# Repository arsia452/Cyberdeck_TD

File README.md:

# Cyberdeck TD Project

## Overview + goal of project
Cyberdeck Project: The main goal is to create a "cyberdeck"; essentially a laptop with personalized functionality, based around the LattePanda Mu compute module.

---

## Main Systems:

### LattePanda Mu Custom Carrier Board:
The cyberdeck is to include a custom carrier PCB to fit the size, needs, and power constraints of the user
- HDMI output
- PCIe M-key for M.2-2230 PCIe 3.0x1 NVMe SSD
- PCIe E-key for Wi-Fi capabilities
- 2x USB-A 2.0 ports
- 2x USB-A 3.2 ports
- GbE (1000Mbps) RJ45 port 
- RTC using CR2032 as CMOS battery

### Custom Keyboard:
The cyberdeck is to include a custom keyboard which can connect over both Bluetooth and an internal 4pin to USB cable.
- Connect over both Bluetooth and USB | Will be achieved using an nRF52840 SoC (henceforth "MCU")
- Built in 1100mAh battery | Will be achieved by using a 2-pin JST connector on the keyboard PCB which powers the MCU and supports USB-C charging
- USB-C connection for both data and charging | Will be achieved by a USB-C port mounted to the keyboard PCB which will allow for both data transmission and charging
- Run ZMK to handle logic and keyboard matrix | Will be achieved by programming the aforementioned MCU and flashing the open-source software to the onboard flash memory

### Battery:
The cyberdeck is to include a built in (~100Wh) battery with safe (but fast) power path charging (can be both on and charging at the same time) and USB-C hot-plug support.
- 100Wh battery | Will be achieved with a Tenergy 14.4V 7000mAh battery pack consisting of 18650 cells in a 4S2P architecture
- Integrated power path charger | Will be achieved with an LTC4612-L42 IC on the main carrier PCB, allowing for smart switching between USB-C system power + charging and exclusive battery power upon plugging in/unplugging the charging cable

### 11.6" Touchscreen:
The cyberdeck is to integrate a 11.6" touchscreen in the housing as well as optional external display.
- Built-in screen | Will be achieved with a DFRobot eDP 11.6" touchscreen to allow for "Microsoft Surface/iPad"-esque capabilities
- External optional display | Will be achieved through HDMI port and software options to allow for mirroring or second monitor extension (1)

### Enclosure:
The cyberdeck is to be enclosed in an enclosure no larger in footprint than a standard laptop (2)
- Custom main enclosure made of machined aluminum and FDM-based 3D printed PLA (3) | Will be achieved with a mixture of outsourced machining capabilities (PCBWay, JLCPCB, etc.) for the aluminum and home 3D printing
- Custom keyboard enclosure made of 3D printed PLA | Will be achieved using home 3D printing capabilities and heat-set inserts to provide increased rigidity.

### Footnotes:

(1) Though, that is pushing the capabilities of the compute module itself

(2) Excluding thickness; that is for a later revision and would require a custom cooling solution, new battery design, and various other technical capabilities that are presently out of reach.

(3) The use of PLA may shift to ABS down the line if the capabilities introduce themselves, but the Bambu Labs A1 I have will not reliably print ABS in open-air environments as ABS is very prone to stringing and deformation in atmospheric conditions. This applies to all mentions of PLA in this project.

---

## Main Components
Excludes passives (Capacitors, diodes, etc.) and materials (PLA, aluminum, solder etc.)
- Main Compute Module | LattePanda Mu
- Development Carrier Board | DFRobot LattePanda Mu Carrier Board Lite (for development and testing purposes)
- Screen | DFRobot 11.6" eDP Touchscreen
- Keyboard PCB | Custom PCB
- Carrier Board PCB | Custom PCB
- Trackpad Module | Azoteq TPS43 
- Keyboard MCU | MDBT50Q-1MV2 (Nordic nRF52840 based SoC)
- Key Switches | Kailh Choc Blue V2
- Keycaps | Undetermined
- Enclosures | Custom designed multi-piece aluminum and PLA construction
- Wi-Fi card | Intel BE200 Wi-Fi 7 and Bluetooth 5.4
- Powerpath Charging | Analog Devices LTC4162-L42 IC
- USB-C Power Delivery | WCH CH224K IC for 20V input
- 3.3V and 5V regulation | Silergy SY8253ADC IC
- Gigabit Ethernet | Realtek RTL8111H-CG
- Sound | Analog Devices MAX98365

---

## Currently Developed:

### Custom Carrier Board:
The carrier board is currently in development. It is now in the final main step; peer review. The ports, SODIMM slot, RTC battery, and battery screw terminal placements are more or less finalized. There may be slight shifts as the development of the enclosure progresses in order to accommodate the screen, keyboard, and battery. The carrier PCB may or may not end up including audio, as I am unsure if the I2S built into the module actually works. Last I heard, it was still in development by DFRobot, so I may need to use USB audio or simply forego internal audio altogether, though that is not ideal.

#### Carrier Board Length Matching:
=-=-=-=-=-=-=- Length Matching -=-=-=-=-=-=-=
Order of precedence:

=-=-=-=-=-=-=- E-key  -=-=-=-=-=-=-=
All in one area  (<0.127mm skew) (0.1704mm trace width):
- CON_PCIE_TX_0 
[0.0000mm] + [0.0000mm] = [0.0000mm] total skew
[2.5690mm] + [104.0946mm] = [106.6636mm] total length

- HSIO_3_RX
[0.0000mm] total skew
[82.0600mm] total length

- REFCLK3
[0.0000mm] total skew
[66.8870mm] total length

=-=-=-=-=-=-=- M-key  -=-=-=-=-=-=-=
All in one area  (<0.127mm skew) (0.1704mm trace width):
- CON_PCIE_TX_1
[0.0000mm] + [0.0000mm] = [0.0000mm] total skew
[2.7606mm] + [109.3664mm] = [112.1270mm] total length

- HSIO_2_RX
[0.0000mm] total skew
[88.0080mm] total length

- REFCLK0
[0.0000mm] total skew
[149.2008mm] total length

=-=-=-=-=-=-=- GbE  -=-=-=-=-=-=-=
All in one area  (<0.127mm skew) (0.1704mm trace width):
- GbE_PCIe_TX 
[0.0055mm] + [0.0000mm] = [0.0055mm] total skew
[1.8168mm] +  [55.2107mm] = [57.0275mm] total length

- GbE_PCIe_RX
[0.0001mm] +  [0.0000mm] = [0.0001mm] total skew
[3.9770mm] +  [49.1530mm] = [53.1300.mm] total length

- GbE_PCIe_CLK
[0.0005mm] total skew
[52.5019mm] total length

 =-=-=-=-=-=-=- HDMI  -=-=-=-=-=-=-=
All in one area (0.10 - 0.15mm skew with pairs also roughly all the same length) (0.1704mm trace width):

The brackets below are in order from HDMI connector to Mu and all of the sub-traces in between the passives.

- DDI_B_TX0 
[0.0001mm] + [0.0000mm] + [0.0001mm] + [0.0000mm] = [0.0002mm] total skew
[3.5389mm] + [4.1628mm] + [4.4761mm] + [94.2515mm] = [106.4293mm] total length

- DDI_B_TX1
[0.0001mm] + [0.0001mm] + [0.0001mm] + [0.0000mm] = [0.0003mm] total skew
[3.5409mm] + [3.7013mm] + [3.9786mm] + [94.2766mm] = [105.4974mm] total length

- DDI_B_TX2
[0.0001mm] + [0.0001mm] + [0.0000mm] + [0.0000mm] = [0.0002mm] total skew
[3.5182mm] + [3.5178mm] + [4.0990mm] + [94.2152mm] = [105.3502mm] total length

- DDI_B_TX3
[0.0001mm] + [0.0000mm] + [0.0001mm] + [0.0000mm] = [0.0002mm] total skew
[3.5170mm] + [4.1919mm] + [4.1763mm] + [94.2153mm] = [106.1005] total length

=-=-=-=-=-=-=- USB3.2  -=-=-=-=-=-=-=
All in one area  (<0.10mm skew) (0.1704mm trace width):
- HSIO_0_TX
[0.0100mm] + [0.0000mm] + [0.0000mm] = [0.0100mm] total skew
[8.8612mm] + [5.3635mm] + [54.0231mm] = [68.2478mm] total length

- HSIO_1_TX
[0.0027mm] + [0.0000mm] + [0.0000mm] = [0.0027mm] total skew
[3.9047mm] + [5.4568mm] + [54.7050mm] = [64.0665mm] total length

- CON_USB3_D 
[0.0000mm] + [0.0000mm] = [0.0000mm] total skew
[29.9915mm] + [84.4885mm] = [114.48mm] total length

- CON_USB4_D
[0.0001mm] + [0.0000mm] = [0.0000mm] total skew
[7.2915mm] + [73.4302mm] = [80.7217mm] total length

- CON_USB3_SSRX
[0.0000mm] + [0.0000mm] = [0.0000mm] total skew
[9.2867mm] + [51.9657mm] = [61.2524mm] total length

- CON_USB4_SSRX
[0.0000mm] + [0.0000mm] = [0.0000mm] total skew
[3.4665mm] + [52.8293mm] = [56.2958mm] total length

=-=-=-=-=-=-=- E-key USB  -=-=-=-=-=-=-=
(<0.10mm skew) (0.1704mm trace width):
- USB_2_P7
[0.0000mm] total skew
[79.0188mm] total length

=-=-=-=-=-=-=- USB2.0  -=-=-=-=-=-=-=
All in one area  (<0.10mm skew (0.1704mm trace width)):
- CON_USB2_D
[0.0000mm] total skew
[59.4753mm] total length

- CON_USB1_D
[0.0000mm] total skew
[66.1903] total length

### Custom Keyboard:
The keyboard PCB is ready for fabrication as soon as the financials make sense. Some other minor modifications may be made based on any lessons learned from the carrier board as development of the two is parallel, but the design is essentially finalized.

### Enclosure
The enclosure itself is the least developed portion of the project thus far. The only thing that it is right now is a couple of STEP models in Fusion360 haphazardly slapped into a shape. 

The keyboard enclosure has been mocked up, but fastening the keyboard enclosure parts together and mounting the keyboard to the main enclosure are still unsolved challenges at this time. Potential approaches for the fastening problem include screws with heat-set inserts, flexible plastic clips, panel clips, snap together clips, or others. The keyboard is currently one massive assembly, but this is infeasible for the 3D printer that I own, and thus must be redesigned from the ground up. A 2-piece assembly is ideal, but a 3-piece assembly will offer more mechanisms to fasten the components together.

### Footnotes: 

(1) Ideally, one chassis part is preferable, but this is likely unfeasible due to home 3D printing size constraints. I will see what I can make happen. Same note as before about PLA/ABS.

---

## Currently in Development:

### Custom Carrier Board:
The battery charging circuitry is yet to be tested, but this will be tested on a standalone PCB with the battery pack I intend to use well before the custom carrier board is finalized for production to ensure that there is no... expedited expulsion of excited electrons and/or lithium due to an incorrect understanding of power-path battery charging and high-side load switching.

### Custom Keyboard:
The MCU, trackpad module, and key switches are currently in the mail (as of 10/16/2026) for further hands-on testing before finalizing the PCB order to ensure proper fit, function, and pinouts as it relates to the MCU _before_ it is set in stone (or fiberglass and copper, I suppose).

### Enclosure
Cooling will be essential, as the battery, compute module and screen will be in the same enclosure in very close proximity to each other. Using an aluminum subframe to diffuse the heat is a possibility, but will require further investigation and development time. The main idea is a five piece enclosure consisting of: faceplate (black anodized aluminum), left side bracket (orange anodized aluminum), right side bracket (orange anodized aluminum), rear main chassis (black 3D printed PLA), front main chassis (black 3D printed PLA) (1)

The keyboard is currently one massive assembly, but this is infeasible for the 3D printer that I own, and thus must be redesigned from the ground up. A 2-piece assembly is ideal for rigidity and simplicity, but a 3-piece assembly will offer more mechanisms to fasten the components together, smaller prints for faster iterative design efforts, and overall more options for design. The 3-piece design is more likely. Fastening the keyboard enclosure parts together and mounting the keyboard to the main enclosure are still unsolved challenges at this time. Potential approaches for the fastening problem include screws with heat-set inserts, flexible plastic clips, panel clips, snap together clips, or others. 3D modeling is not yet something I am very good at, so this will be a good chance to improve my skills in a useful and fun way. Potential approaches to the mounting issue are rails, slots, or grooves on the main enclosure that the keyboard slides into, magnets, or others.

### Footnotes: 

(1) Ideally, one main chassis is preferable for the sake of rigidity and solid construction feel, but this is likely unfeasible due to home 3D printing size constraints. I will see what I can make happen. Same note as before about PLA/ABS.

---

## Future of Development/Improvements for Next Iteration:

---

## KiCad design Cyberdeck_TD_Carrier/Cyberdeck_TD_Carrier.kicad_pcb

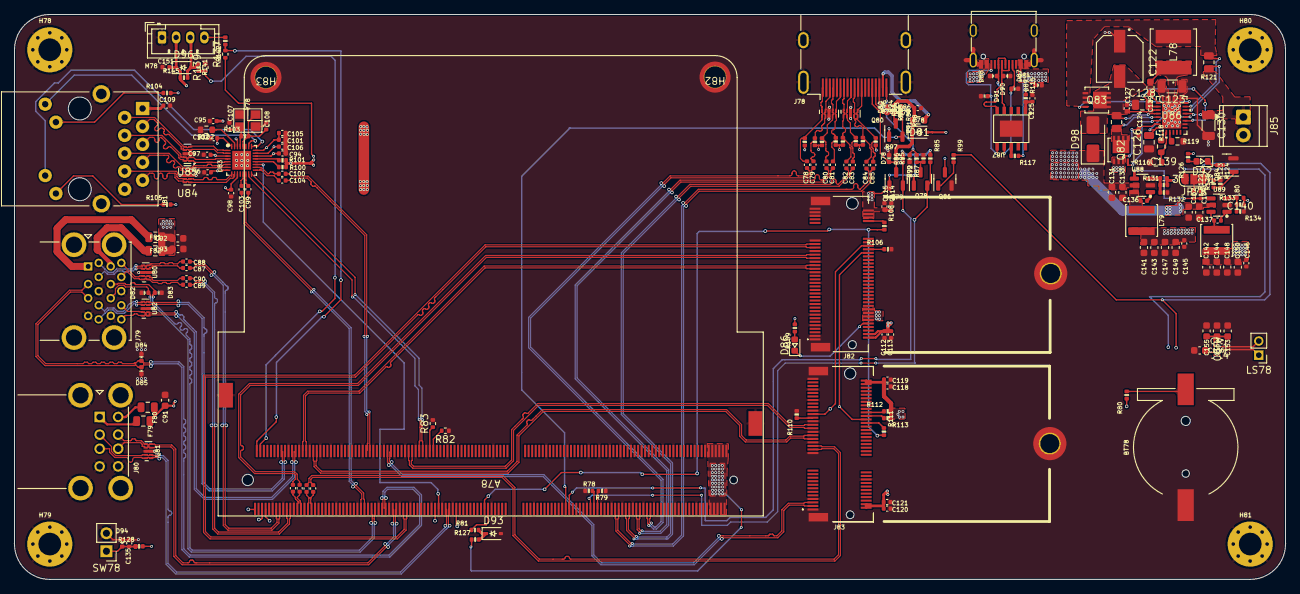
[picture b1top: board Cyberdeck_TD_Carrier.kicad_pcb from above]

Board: 4 copper layers, 180.0 x 80.0 mm, 205 parts (0 on the bottom side), 166 nets.

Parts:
A78: LattePanda_Mu; LattePanda_Module_H8.0mm_Horizontal
BT78: Battery_Cell; Battery_Holder_CR1220_S8411-45R
C78, C79, C80, C81, C82, C83, C84, C85, C86, C87, C88, C89, C90, C94, C95, C96, C97, C98, C99, C100, C101, C102, C103, C104, C106, C109, C113, C115, C119, C121, C136, C137, C145, C146, C151: 100nF/50V; C_0402_1005Metric
C91, C92, C93, C131, C132, C133, C134, C141, C142, C143, C144, C147, C148, C149, C150: 22uF/10V; C_0603_1608Metric
C105, C112, C114, C118, C120: 10uF/10V; C_0402_1005Metric
C107, C108, C139, C140: 12pF/50V; C_0402_1005Metric
C110, C111, C116, C117: 220nF/50V; C_0402_1005Metric
C122: 47uF; CAP_EEEFH1E470XL
C123, C130: 10uF; C_1206_3216Metric
C124, C127: 0.1uF; C_0402_1005Metric
C125, C135: 1uF/16V; C_0402_1005Metric
C126: 1uF; C_0805_2012Metric
C128: 10uF; C_0805_2012Metric
C129: 22nF; C_0603_1608Metric
C153: 100uF; C_0603_1608Metric
C154: 10uF; C_0603_1608Metric
C155, C156: 1uF; C_0603_1608Metric
D78, D79, D80, D82, D83, D84, D85, D87, D88, D94: ESD5V0B03; D_0402_1005Metric
D81, D96: 1N5819WS; D_SOD-323
D86, D92: LED_G; LED_0603_1608Metric
D89, D90, D91: PESD24VS1UL-N; D_0402_1005Metric
D93: 3V3 Izt=5mA; D_SOD-323
D98: D_TVS; D_SMA
F78: 6V/50mA; R_0603_1608Metric
F79, F80: 6V/1A; Fuse_0805_2012Metric
F81: 6V/2A; R_0805_2012Metric
F82: 6V/2A; Fuse_0805_2012Metric
H78, H79, H80, H81: MountingHole_Pad; MountingHole_3.2mm_M3_Pad_Via
H82, H83: MountingHole_Pad; MountingHole_3mm_M2_Pad_TopOnly
H84, H85: MountingHole_M2.0; MountingHole_2.7mm_M2.5_DIN965_Pad_TopOnly
J78: HDMI_A; HDMI_A_Molex_208658-1001_Horizontal
J79: USB3_A_Stacked; USB3_A_Molex_48406-0001_Horizontal_Stacked
J80: USB_A_Stacked; USB_A_CUI_UJ2-ADH-TH_Horizontal_Stacked
J81: RJ45_RB1-125B8G1A; RJ45_UDE_RB1-125B8G1A
J82: Bus_M.2_Socket_M; PCIe_M.2_Connectors_P=0.5mm_H=4.2mm_KeyM
J83: Bus_M.2_Socket_E; PCIe_M.2_Connectors_P=0.5mm_H=4.2mm_KeyE
J84: USB_C_Receptacle_USB2.0; USB_C_Receptacle_G-Switch_GT-USB-7010ASV
J85: BAT_TERM; TerminalBlock_TE_282834-2_1x02_P2.54mm_Horizontal
JP78: SolderJumper_3_Open; SolderJumper-3_P1.3mm_Bridged2Bar12_RoundedPad1.0x1.5mm_Num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
L78: 4.7uH; IND_VLS6045EX-4R7M_TDK
L79, L80: 2.2uH/4.3A; L_Sunlord_SWPA4020S
LS78: Speaker; PinHeader_1x02_P2.00mm_Vertical
M78: Fan_4pin; JST_PH_B4B-PH-K_1x04_P2.00mm_Vertical
Q78, Q84: 2N7002; SOT-23
Q79, Q80, Q81: 2SK3018; SOT-23
Q82, Q83: FDMC8327L; WDFN8_511DR_OSI
R78, R79, R125: 100K/1%; R_0402_1005Metric
R80, R92, R115, R123: 1K/1%; R_0402_1005Metric
R81, R82, R83, R100, R101, R112, R113, R117, R124, R132: 10K/1%; R_0402_1005Metric
R84, R86, R95, R98, R99, R109, R126, R127: 2.2K/1%; R_0402_1005Metric
R85, R103: 1M/1%; R_0402_1005Metric
R87, R133, R139, R141: 21.5K/1%; R_0402_1005Metric
R88, R89, R90, R91, R93, R94, R96, R97, R104, R105: 470R/1%; R_0402_1005Metric
R102: 2.49K/1%; R_0603_1608Metric
R106, R108, R110, R111: 0R/1%; R_0402_1005Metric
R114: 6.8mΩ; R_0805_2012Metric
R116, R118: 10kΩ; R_0603_1608Metric
R119: 63.4kΩ; R_0603_1608Metric
R121: 10mΩ; R_0805_2012Metric
R122, R128, R142: 100R/1%; R_0402_1005Metric
R131: 75K/1%; R_0402_1005Metric
R134, R137, R145: 4.7K/1%; R_0402_1005Metric
SW78: PWR_BTN; PinHeader_1x02_P2.54mm_Vertical
U78, U79: TPAZ1023-04F; Diodes_UDFN-10_1.0x2.5mm_P0.5mm
U80, U81, U82, U84, U85: ULC0524P; Diodes_UDFN-10_1.0x2.5mm_P0.5mm
U83: RTL8111H-CG-RH; QFN-32-1EP_4x4mm_P0.4mm_EP2.65x2.65mm
U86: LTC4162-L42; 05-08-1712_ADI-L
U87: CH224K; ESSOP-10-1EP_3.9x5mm_P1.0mm_EP3.2x2.3
U88, U89: SY8253ADC; TSOT-23-6
U90: MAX98365AEWC+; 21-100536_W121D1&plus_1_MXM
Y78: 25MHz; Crystal_SMD_3225-4Pin_3.2x2.5mm

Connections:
5V_HDMI_VCC: C86.1, D81.1 (K), F78.1, R95.1, R98.1
+1V0: C94.2, C95.2, C96.2, C97.2, C101.2, C105.2, U83.3 (AVDD10), U83.8 (AVDD10), U83.22 (DVDD10), U83.24 (REGOUT), U83.30 (AVDD10)
+3V3: C98.2, C102.2, C106.2, C112.2, C113.2, C114.2, C115.2, C118.2, C119.2, C120.2, C121.2, C140.1, C142.2, C144.2, C146.1, C148.2, C150.2, J82.2 (3.3V), J82.4 (3.3V), J82.12 (3.3V), J82.14 (3.3V), J82.16 (3.3V), J82.18 (3.3V), J82.70 (3.3V), J82.72 (3.3V), J82.74 (3.3V), J83.2 (3.3V), J83.4 (3.3V), J83.72 (3.3V), J83.74 (3.3V), L80.2, Q78.1 (G), Q79.1 (G), Q80.1 (G), R84.1, R85.1, R86.1, R100.1, R101.1, R104.2, R105.2, R109.2, R112.2, R113.1, R126.2, R133.2, R137.1, U83.11 (AVDD33), U83.23 (VDDREG), U83.32 (AVDD33)
+5V: C91.2, C92.2, C93.2, C139.1, C141.2, C143.2, C145.1, C147.2, C149.2, C151.1, D81.2 (A), D96.1 (K), F79.1, F80.1, F81.1, F82.1, L79.2, M78.2 (+), R131.2, R145.1
+BATT: A78.115 (VBAT), R80.1
/Fan_Temp/FAN_1_PWM: A78.2 (FAN1_PWM), R137.2, R142.1
/Fan_Temp/FAN_1_TAC: A78.4 (FAN1_TAC), R139.1, R141.2
/Gigabit Ethernet/GbE_PCIe_CLK+: A78.94 (REFCLK4+), U83.15 (REFCLK_P)
/Gigabit Ethernet/GbE_PCIe_CLK-: A78.96 (REFCLK4-), U83.16 (REFCLK_N)
/Gigabit Ethernet/GbE_PCIe_RX+: A78.64 (HSIO6_RX+), C104.2
/Gigabit Ethernet/GbE_PCIe_RX-: A78.66 (HSIO6_RX-), C100.2
/Gigabit Ethernet/GbE_PCIe_TX+: A78.61 (HSIO6_TX+), C103.2
/Gigabit Ethernet/GbE_PCIe_TX-: A78.63 (HSIO6_TX-), C99.2
/Gigabit Ethernet/HSI+: C103.1, U83.13 (HSIP)
/Gigabit Ethernet/HSI-: C99.1, U83.14 (HSIN)
/Gigabit Ethernet/HSO+: C104.1, U83.17 (HSOP)
/Gigabit Ethernet/HSO-: C100.1, U83.18 (HSON)
/Gigabit Ethernet/LED1_1000: J81.L4, U83.26 (LED1)
/Gigabit Ethernet/LED2_ACT: J81.L2, U83.25 (LED2)
/Gigabit Ethernet/MDI0+: J81.R2 (TD1+), U83.1 (MDIP0), U85.5, U85.6 (NC)
/Gigabit Ethernet/MDI0-: J81.R3 (TD1-), U83.2 (MDIN0), U85.4, U85.7 (NC)
/Gigabit Ethernet/MDI1+: J81.R4 (TD2+), U83.4 (MDIP1), U85.2, U85.9 (NC)
/Gigabit Ethernet/MDI1-: J81.R5 (TD2-), U83.5 (MDIN1), U85.1, U85.10 (NC)
/Gigabit Ethernet/MDI2+: J81.R6 (TD3+), U83.6 (MDIP2), U84.5, U84.6 (NC)
/Gigabit Ethernet/MDI2-: J81.R7 (TD3-), U83.7 (MDIN2), U84.4, U84.7 (NC)
/Gigabit Ethernet/MDI3+: J81.R8 (TD4+), U83.9 (MDIP3), U84.2, U84.9 (NC)
/Gigabit Ethernet/MDI3-: J81.R9 (TD4-), U83.10 (MDIN3), U84.1, U84.10 (NC)
/HDMI/DDC_SCL: D78.2 (A2), J78.15 (SCL), Q79.3 (D), R95.2
/HDMI/DDC_SDA: D80.2 (A2), J78.16 (SDA), Q80.3 (D), R98.2
/HDMI/DDI_B_DDC_SCL: A78.171 (DDIB_DDC_SCL), Q79.2 (S), R86.2
/HDMI/DDI_B_DDC_SDA: A78.169 (DDIB_DDC_SDA), Q80.2 (S), R84.2
/HDMI/DDI_B_HPD: A78.183 (DDIB_HPD), Q78.2 (S), R85.2
/HDMI/DDI_B_TX0+: A78.217 (DDIB_TX0+), C78.1
/HDMI/DDI_B_TX0-: A78.215 (DDIB_TX0-), C79.1
/HDMI/DDI_B_TX1+: A78.211 (DDIB_TX1+), C80.1
/HDMI/DDI_B_TX1-: A78.209 (DDIB_TX1-), C81.1
/HDMI/DDI_B_TX2+: A78.205 (DDIB_TX2+), C82.1
/HDMI/DDI_B_TX2-: A78.203 (DDIB_TX2-), C83.1
/HDMI/DDI_B_TX3+: A78.199 (DDIB_TX3+), C84.1
/HDMI/DDI_B_TX3-: A78.197 (DDIB_TX3-), C85.1
/HDMI/HPD: D79.2 (A2), J78.19 (HPD), R92.2
/HDMI/TMDS_CK+: C84.2, J78.10 (CK+), R89.1, U79.4, U79.7 (NC)
/HDMI/TMDS_CK-: C85.2, J78.12 (CK-), R88.1, U79.5, U79.6 (NC)
/HDMI/TMDS_D0+: C82.2, J78.7 (D0+), R91.1, U79.1, U79.10 (NC)
/HDMI/TMDS_D0-: C83.2, J78.9 (D0-), R90.1, U79.2, U79.9 (NC)
/HDMI/TMDS_D1+: C80.2, J78.4 (D1+), R94.1, U78.4, U78.7 (NC)
/HDMI/TMDS_D1-: C81.2, J78.6 (D1-), R93.1, U78.5, U78.6 (NC)
/HDMI/TMDS_D2+: C78.2, J78.1 (D2+), R97.1, U78.1, U78.10 (NC)
/HDMI/TMDS_D2-: C79.2, J78.3 (D2-), R96.1, U78.2, U78.9 (NC)
/LattePanda Module/HSIO_0_TX+: A78.13 (HSIO0_TX+), C88.1
/LattePanda Module/HSIO_0_TX-: A78.15 (HSIO0_TX-), C87.1
/LattePanda Module/HSIO_1_TX+: A78.19 (HSIO1_TX+), C90.1
/LattePanda Module/HSIO_1_TX-: A78.21 (HSIO1_TX-), C89.1
/LattePanda Module/HSIO_2_RX+: A78.28 (HSIO2_RX+), J82.43 (PERp0/SATA-B-)
/LattePanda Module/HSIO_2_RX-: A78.30 (HSIO2_RX-), J82.41 (PERn0/SATA-B+)
/LattePanda Module/HSIO_2_TX+: A78.25 (HSIO2_TX+), C110.1
/LattePanda Module/HSIO_2_TX-: A78.27 (HSIO2_TX-), C111.1
/LattePanda Module/HSIO_3_RX+: A78.34 (HSIO3_RX+), J83.41 (PERp0)
/LattePanda Module/HSIO_3_RX-: A78.36 (HSIO3_RX-), J83.43 (PERn0)
/LattePanda Module/HSIO_3_TX+: A78.31 (HSIO3_TX+), C116.1
/LattePanda Module/HSIO_3_TX-: A78.33 (HSIO3_TX-), C117.1
/LattePanda Module/REFCLK0+: A78.85 (REFCLK0+), J82.53 (REFCLKn)
/LattePanda Module/REFCLK0-: A78.87 (REFCLK0-), J82.55 (REFCLKp)
/LattePanda Module/REFCLK3+: A78.88 (REFCLK3+), J83.47 (REFCLKp0)
/LattePanda Module/REFCLK3-: A78.90 (REFCLK3-), J83.49 (REFCLKn0)
/LattePanda Module/SLS_S3: A78.7 (SLS_S3), JP78.3 (B)
/LattePanda Module/SUSCLK_WIFI: A78.131 (SUSCLK), R108.2, R111.2
/LattePanda Module/USB_2_P7+: A78.76 (USB2_P7+), J83.3 (USB_D+)
/LattePanda Module/USB_2_P7-: A78.78 (USB2_P7-), J83.5 (USB_D-)
/LattePanda Module/~PWR_SW: A78.1 (~PWRBTN), R128.2
/M.2 E&M Key/CON_PCIE_TX_0+: C116.2, J83.35 (PETp0)
/M.2 E&M Key/CON_PCIE_TX_0-: C117.2, J83.37 (PETn0)
/M.2 E&M Key/CON_PCIE_TX_1+: C110.2, J82.49 (PETp0/SATA-A+)
/M.2 E&M Key/CON_PCIE_TX_1-: C111.2, J82.47 (PETn0/SATA-A-)
/M.2 E&M Key/~CLKREQE: J83.53 (~CLKREQ0), R110.1
/M.2 E&M Key/~CLKREQM: J82.52 (~CLKREQ), R106.1
/PSU/BAT(+): C130.1, J85.1 (B(+)), R121.2, U86.19 (BATSENS+), U86.20 (CSN)
/PSU/BATFET: Q83.4, U86.22 (BATFET)
/PSU/BIAS: R118.2, U86.9 (NTCBIAS)
/PSU/BOOST: C129.2, U86.1 (BOOST)
/PSU/CC1: D90.1 (K), J84.A5 (CC1), U87.7 (CC1)
/PSU/CC2: D91.1 (K), J84.B5 (CC2), U87.6 (CC2)
/PSU/CELLS0: C128.2, U86.2 (INTVCC), U86.17 (CELLS0)
/PSU/CELLS1: C126.2, U86.8 (VCC2P5), U86.18 (CELLS1)
/PSU/CLP: Q82.5, Q82.6, Q82.7, Q82.8, R114.2, U86.5 (CLP)
/PSU/CSP: L78.2, Q83.1, Q83.2, Q83.3, R121.1, U86.21 (CSP)
/PSU/INFET: Q82.4, U86.6 (INFET)
/PSU/NTC: R116.1, R118.1, U86.10 (NTC)
/PSU/PWR_C_D+: D88.2 (A2), J84.A6 (D+), J84.B6 (D+), U87.4 (DP)
/PSU/PWR_C_D-: D87.2 (A2), J84.A7 (D-), J84.B7 (D-), U87.5 (DM)
/PSU/PWR_EN: R122.2, R125.2, U88.4 (EN), U89.4 (EN)
/PSU/RT: R119.1, U86.11 (RT)
/PSU/SW: C129.1, L78.1, U86.25 (SW), U86.26 (SW)
/PSU/VBUS: C124.1, D89.1 (K), J84.A4 (VBUS), J84.A9 (VBUS), J84.B4 (VBUS), J84.B9 (VBUS), Q82.1, Q82.2, Q82.3, R115.1, R117.1, U86.7 (VIN)
/USB2.0&USB3.0/CON_USB1_D_N: A78.109 (USB2_P5-), J80.2 (D1-), U81.2, U81.9 (NC)
/USB2.0&USB3.0/CON_USB1_D_P: A78.111 (USB2_P5+), J80.3 (D1+), U81.1, U81.10 (NC)
/USB2.0&USB3.0/CON_USB2_D_N: A78.79 (USB2_P3-), J80.6 (D2-), U81.5, U81.6 (NC)
/USB2.0&USB3.0/CON_USB2_D_P: A78.81 (USB2_P3+), J80.7 (D2+), U81.4, U81.7 (NC)
/USB2.0&USB3.0/CON_USB3_D_N: A78.73 (USB2_P2-), D85.2 (A2), J79.2 (D1-)
/USB2.0&USB3.0/CON_USB3_D_P: A78.75 (USB2_P2+), D84.2 (A2), J79.3 (D1+)
/USB2.0&USB3.0/CON_USB3_SSRX_N: A78.18 (HSIO0_RX-), J79.5 (SSRX1-), U82.4, U82.7 (NC)
/USB2.0&USB3.0/CON_USB3_SSRX_P: A78.16 (HSIO0_RX+), J79.6 (SSRX1+), U82.5, U82.6 (NC)
/USB2.0&USB3.0/CON_USB3_SSTX_N: C87.2, J79.8 (SSTX1-), U80.4, U80.7 (NC)
/USB2.0&USB3.0/CON_USB3_SSTX_P: C88.2, J79.9 (SSTX1+), U80.5, U80.6 (NC)
/USB2.0&USB3.0/CON_USB4_D_N: A78.67 (USB2_P1-), D83.2 (A2), J79.11 (D2-)
/USB2.0&USB3.0/CON_USB4_D_P: A78.69 (USB2_P1+), D82.2 (A2), J79.12 (D2+)
/USB2.0&USB3.0/CON_USB4_SSRX_N: A78.24 (HSIO1_RX-), J79.14 (SSRX2-), U82.1, U82.10 (NC)
/USB2.0&USB3.0/CON_USB4_SSRX_P: A78.22 (HSIO1_RX+), J79.15 (SSRX2+), U82.2, U82.9 (NC)
/USB2.0&USB3.0/CON_USB4_SSTX_N: C89.2, J79.17 (SSTX2-), U80.1, U80.10 (NC)
/USB2.0&USB3.0/CON_USB4_SSTX_P: C90.2, J79.18 (SSTX2+), U80.2, U80.9 (NC)
/~PLT_RST: A78.105 (~PLTRST), J82.50 (~PERST), J83.52 (~PERST0), U83.19 (PERSTB)
/~PWR_LED/~PSON: A78.5 (SLS_S0), JP78.1 (A), R99.1, R123.1
/~WAKE: A78.103 (~WAKE), J82.54 (~PEWAKE), J83.55 (~PEWAKE0)
AUDIO: A78.166 (I2S_TXD), U90.B4 (DAI1)
BCLK: A78.162 (I2S_SCLK), U90.C4 (DAI0)
FCLK: A78.164 (I2S_SFRM), U90.A4 (DAI2)
GND: A78.11 (GND), A78.14 (GND), A78.17 (GND), A78.20 (GND), A78.23 (GND), A78.26 (GND), A78.29 (GND), A78.32 (GND), A78.35 (GND), A78.38 (GND), A78.41 (GND), A78.44 (GND), A78.47 (GND), A78.50 (GND), A78.53 (GND), A78.56 (GND), A78.59 (GND), A78.62 (GND), A78.65 (GND), A78.68 (GND), A78.71 (GND), A78.74 (GND), A78.77 (GND), A78.80 (GND), A78.83 (GND), A78.86 (GND), A78.89 (GND), A78.92 (GND), A78.95 (GND), A78.98 (GND), A78.101 (GND), A78.107 (GND), A78.110 (GND), A78.113 (GND), A78.116 (GND), A78.135 (GND), A78.136 (GND), A78.151 (GND), A78.158 (GND), A78.167 (GND), A78.170 (GND), A78.181 (GND), A78.182 (GND), A78.188 (GND), A78.189 (GND), A78.194 (GND), A78.195 (GND), A78.200 (GND), A78.201 (GND), A78.206 (GND), A78.207 (GND), A78.212 (GND), A78.213 (GND), A78.218 (GND), A78.219 (GND), A78.224 (GND), A78.225 (GND), A78.230 (GND), A78.231 (GND), A78.236 (GND), A78.237 (GND), A78.242 (GND), A78.243 (GND), A78.248 (GND), A78.249 (GND), A78.MP (Mountinge_Pads), BT78.2 (-), C86.2, C91.1, C92.1, C93.1, C94.1, C95.1, C96.1, C97.1, C98.1, C101.1, C102.1, C105.1, C106.1, C107.1, C108.1, C109.2, C112.1, C113.1, C114.1, C115.1, C118.1, C119.1, C120.1, C121.1, C122.1, C123.1, C124.2, C125.2, C126.1, C127.1, C128.1, C130.2, C131.1, C132.1, C133.1, C134.1, C135.2, C141.1, C142.1, C143.1, C144.1, C145.2, C146.2, C147.1, C148.1, C149.1, C150.1, C151.2, C153.1, C154.1, C155.1, C156.1, D78.1 (A1), D79.1 (A1), D80.1 (A1), D82.1 (A1), D83.1 (A1), D84.1 (A1), D85.1 (A1), D87.1 (A1), D88.1 (A1), D89.2 (A), D90.2 (A), D91.2 (A), D93.2 (A), D94.1 (A1), H78.1, H79.1, H80.1, H81.1, H82.1, H83.1, H84.1, H85.1, J78.2 (D2S), J78.5 (D1S), J78.8 (D0S), J78.11 (CKS), J78.17 (GND), J78.SH, J79.4 (GND1), J79.7 (DRAIN1), J79.13 (GND2), J79.16 (DRAIN2), J79.19 (SHIELD), J80.4 (GND1), J80.8 (GND2), J80.9 (Shield), J81.R10 (GND), J81.SH, J82.1 (GND), J82.3 (GND), J82.9 (GND), J82.15 (GND), J82.21 (GND), J82.27 (GND), J82.33 (GND), J82.39 (GND), J82.45 (GND), J82.51 (GND), J82.57 (GND), J82.71 (GND), J82.73 (GND), J82.75 (GND), J82.MP1, J82.MP2, J83.1 (GND), J83.7 (GND), J83.18 (GND), J83.33 (GND), J83.39 (GND), J83.45 (GND), J83.51 (GND), J83.57 (GND), J83.63 (GND), J83.69 (GND), J83.75 (GND), J83.MP1, J83.MP2, J84.A1 (GND), J84.A12 (GND), J84.B1 (GND), J84.B12 (GND), J84.S1 (SHIELD), J85.2 (B(-)), M78.1 (-), Q81.2 (S), Q84.2 (S), R78.2, R79.2, R82.2, R83.2, R87.2, R102.1, R106.2, R110.2, R116.2, R119.2, R124.1, R125.1, R132.1, R134.1, R139.2, SW78.2, U78.3 (VSS), U78.8 (VSS), U79.3 (VSS), U79.8 (VSS), U80.3 (VSS), U80.8 (VSS), U81.3 (VSS), U81.8 (VSS), U82.3 (VSS), U82.8 (VSS), U83.33 (GND), U84.3 (VSS), U84.8 (VSS), U85.3 (VSS), U85.8 (VSS), U86.16 (SYNC), U86.23 (PGND), U86.24 (PGND), U86.29 (AGND), U87.0 (GND), U88.2 (GND), U89.2 (GND), U90.B2 (GND), U90.C2 (GND), Y78.2, Y78.4
unnamed: A78.187 (TCP0_HPD), R78.1
unnamed: A78.185 (TCP1_HPD), R79.1
unnamed: A78.133 (~BIOS_SEL), R81.1
unnamed: A78.100 (~CLKREQ3), R83.1
unnamed: A78.102 (~CLKREQ4), R82.1
unnamed: BT78.1 (+), R80.2
unnamed: C153.2, C154.2, C155.2, U90.B1 (PVDD), U90.C1 (PVDD)
unnamed: D86.2 (A), R109.1
unnamed: D86.1 (K), J82.10 (DAS/~DSS/~LED1)
unnamed: D92.2 (A), R126.1
unnamed: D92.1 (K), Q84.3 (D)
unnamed: C135.1, D94.2 (A2), R128.1, SW78.1
unnamed: D96.2 (A), M78.3 (Tacho), R141.1, R145.2
unnamed: F78.2, J78.18 (+5V)
unnamed: F81.2, J79.1 (VBUS1)
unnamed: F82.2, J79.10 (VBUS2)
unnamed: F79.2, J80.1 (VBUS1)
unnamed: F80.2, J80.5 (VBUS2)
unnamed: C109.1, J81.R1 (CT)
unnamed: J81.L1, R105.1
unnamed: J81.L3, R104.1
unnamed: J82.68 (SUSCLK), R108.1
unnamed: J83.50 (SUSCLK), R111.1
unnamed: J83.56 (~W_DISABLE1), R112.1
unnamed: J83.54 (~W_DISABLE2), R113.2
unnamed: JP78.2 (C), R122.1
unnamed: M78.4 (PWM), R142.2
unnamed: Q78.3 (D), R87.1, R92.1
unnamed: Q81.3 (D), R88.2, R89.2, R90.2, R91.2, R93.2, R94.2, R96.2, R97.2
unnamed: Q81.1 (G), R99.2
unnamed: Q84.1 (G), R123.2, R124.2
unnamed: C108.2, R103.2, U83.28 (CKXTAL1), Y78.1
unnamed: C107.2, R103.1, U83.29 (CKXTAL2), Y78.3
unnamed: R100.2, U83.20 (ISOLATEB)
unnamed: R101.2, U83.21 (LANWAKEB)
unnamed: R102.2, U83.31 (RSET)
unnamed: R117.2, U87.8 (VBUS)
unnamed: C125.1, R115.2, U87.1 (VDD)
unnamed: C136.2, U88.1 (BOOST)
unnamed: C139.2, R131.1, R132.2, U88.3 (FB)
unnamed: C136.1, L79.1, U88.6 (SW)
unnamed: C137.2, U89.1 (BOOST)
unnamed: C140.2, R133.1, R134.2, U89.3 (FB)
unnamed: C137.1, L80.1, U89.6 (SW)
unnamed: LS78.1, U90.A2 (OUTN)
unnamed: LS78.2, U90.A1 (OUTP)
unnamed: C156.2, U90.C3 (VDD)
VDC: A78.250 (VIN), A78.251 (VIN), A78.252 (VIN), A78.253 (VIN), A78.254 (VIN), A78.255 (VIN), A78.256 (VIN), A78.257 (VIN), A78.258 (VIN), A78.259 (VIN), A78.260 (VIN), C122.2, C123.2, C127.2, C131.2, C132.2, C133.2, C134.2, D98.1 (A1), D98.2 (A2), Q83.5, Q83.6, Q83.7, Q83.8, R114.1, R127.1, U86.3 (VOUTA), U86.4 (CLN), U86.27 (VOUT), U86.28 (VOUT), U88.5 (VIN), U89.5 (VIN)
VPullup: D93.1 (K), R81.2, R127.2
